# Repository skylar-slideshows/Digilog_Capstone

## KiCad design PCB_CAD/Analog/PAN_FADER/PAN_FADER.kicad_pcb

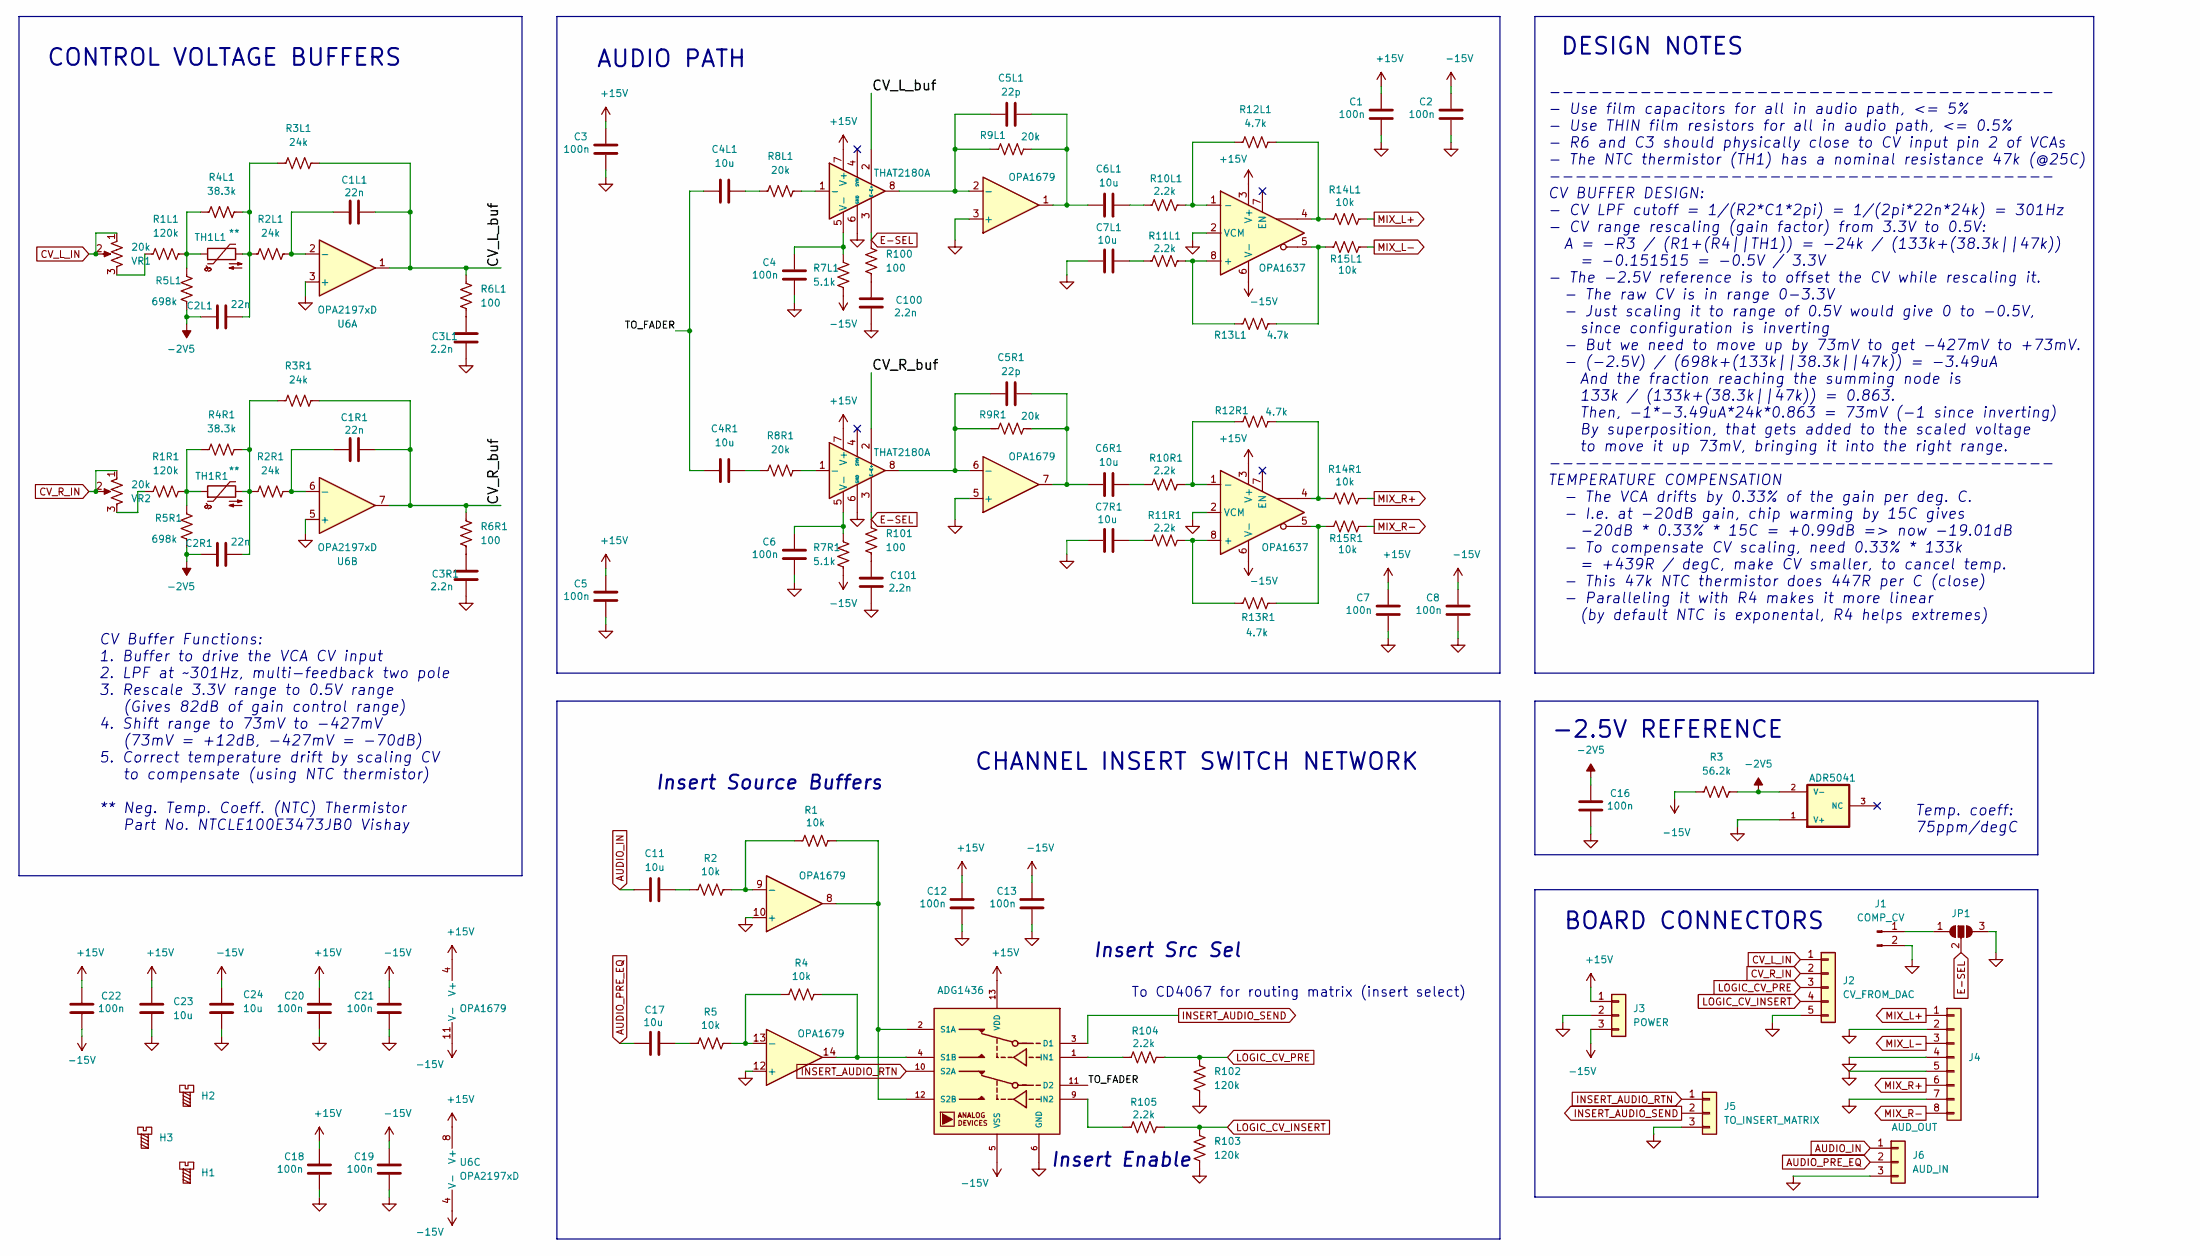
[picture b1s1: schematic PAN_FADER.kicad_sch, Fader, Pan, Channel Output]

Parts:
C1, C2, C3, C4, C5, C6, C7, C8, C12, C13, C16, C18, C19, C20, C21, C22: 100n; C_0603_1608Metric; LCSC C1591
C1L1, C1R1, C2L1, C2R1: 22n; C_Rect_L7.2mm_W2.5mm_P5.00mm; LCSC DNP
C3L1, C3R1, C100, C101: 2.2n; C_0805_2012Metric; LCSC C107103
C4L1, C4R1, C6L1, C6R1, C7L1, C7R1, C11, C17: 10u; CP_Elec_6.3x5.4_Nichicon; LCSC C340735
C5L1, C5R1: 22p; C_0603_1608Metric; LCSC C105620
C23, C24: 10u; C_1206_3216Metric; LCSC C9807
H1, H2, H3: MountingHole_Pad; MountingHole_2.2mm_M2
J1: COMP_CV; PinHeader_1x02_P2.54mm_Vertical; LCSC DNP
J2: CV_FROM_DAC; PinHeader_1x05_P2.54mm_Vertical; Part Number 1-0301FBV0T; LCSC DNP
J3: POWER; PinHeader_1x03_P2.54mm_Vertical; Part Number 1-0301FBV0T; LCSC DNP
J4: AUD_OUT; PinHeader_1x08_P2.54mm_Vertical; Part Number 1-0301FBV0T; LCSC DNP
J5: TO_INSERT_MATRIX; PinHeader_1x03_P2.54mm_Vertical; Part Number 1-0301FBV0T; LCSC DNP
J6: AUD_IN; PinHeader_1x03_P2.54mm_Vertical; Part Number 1-0301FBV0T; LCSC DNP
JP1: SolderJumper_3_Open; SolderJumper-3_P2.0mm_Open_TrianglePad1.0x1.5mm; LCSC DNP
R1, R2, R4, R5, R14L1, R14R1, R15L1, R15R1: 10k; R_0603_1608Metric; LCSC C95204
R1L1, R1R1, R102, R103: 120k; R_0402_1005Metric; LCSC C517522
R2L1, R2R1, R3L1, R3R1: 24k; R_0603_1608Metric; LCSC C319717
R3: 56.2k; R_0402_1005Metric; LCSC C705626
R4L1, R4R1: 38.3k; R_0603_1608Metric; LCSC C861362
R5L1, R5R1: 698k; R_0805_2012Metric; LCSC C865618
R6L1, R6R1, R100, R101: 100; R_0603_1608Metric; LCSC C22775
R7L1, R7R1: 5.1k; R_0603_1608Metric; LCSC C122969
R8L1, R8R1, R9L1, R9R1: 20k; R_0603_1608Metric; LCSC C154077
R10L1, R10R1, R11L1, R11R1, R104, R105: 2.2k; R_0402_1005Metric; LCSC C326602
R12L1, R12R1, R13L1, R13R1: 4.7k; R_0402_1005Metric; LCSC C281778
TH1L1, TH1R1: **; R_Axial_DIN0207_L6.3mm_D2.5mm_P2.54mm_Vertical; LCSC DNP
U1, U5: THAT2180A; SIP-8_19x3mm_P2.54mm; LCSC DNP
U2: OPA1679; SOIC-14_3.9x8.65mm_Pitch1.27mm; LCSC C2878631
U3, U7: OPA1637; Texas_S-PDSO-G8_3x3mm_P0.65mm; LCSC C2860968
U6: OPA2197xD; SOIC-8_3.9x4.9mm_P1.27mm; LCSC C139363
U8: ADR5041; SOT-23-3; MPN ADR5041ARTZ-R2; LCSC C659596
U9: ADG1436; TSSOP-16_4.4x5mm_P0.65mm; LCSC C408899
VR1, VR2: 20k; Potentiometer_Bourns_3314J_Vertical; LCSC C55069

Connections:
+15V: C1.2, C3.2, C5.2, C7.2, C12.2, C18.2, C20.2, C22.2, C23.1, J3.1, U1.7 (V+), U2.4 (V+), U3.3 (V+), U5.7 (V+), U6.8 (V+), U7.3 (V+), U9.13 (VDD)
-2V5: C2L1.1, C2R1.1, C16.2, R3.2, R5L1.1, R5R1.1, U8.2 (V-)
-15V: C2.2, C8.2, C13.2, C19.2, C21.2, C22.1, C24.2, J3.3, R3.1, R7L1.1, R7R1.1, U2.11 (V-), U3.6 (V-), U6.4 (V-), U7.6 (V-), U9.5 (VSS)
/CV_L_buf: C1L1.2, R3L1.2, R6L1.2, U1.2 (E+), U6.1
/CV_R_buf: C1R1.2, R3R1.2, R6R1.2, U5.2 (E+), U6.7
/TO_FADER: C4L1.1, C4R1.1, U9.11 (D2)
AUDIO_IN: C11.1, J6.1
AUDIO_PRE_EQ: C17.1, J6.2
CV_L_IN: J2.1, VR1.1, VR1.2
CV_R_IN: J2.2, VR2.1, VR2.2
E-SEL: JP1.2 (C), R100.2, R101.2, U1.3 (E-), U5.3 (E-)
GND: C1.1, C2.1, C3.1, C3L1.1, C3R1.1, C4.1, C5.1, C6.1, C7.1, C7L1.1, C7R1.1, C8.1, C12.1, C13.1, C16.1, C18.1, C19.1, C20.1, C21.1, C23.2, C24.1, C100.1, C101.1, J1.2, J2.5, J3.2, J4.2, J4.4, J4.5, J4.7, J5.3, J6.3, JP1.3 (B), R102.1, R103.1, U1.6 (GND), U2.3 (+), U2.5 (+), U2.10 (+), U2.12 (+), U3.2 (VCM), U5.6 (GND), U6.3 (+), U6.5 (+), U7.2 (VCM), U8.1 (V+), U9.6 (GND)
INSERT_AUDIO_RTN: J5.1, U9.10 (S2A)
INSERT_AUDIO_SEND: J5.2, U9.3 (D1)
LOGIC_CV_INSERT: J2.4, R103.2, R105.2
LOGIC_CV_PRE: J2.3, R102.2, R104.2
MIX_L+: J4.1, R14L1.2
MIX_L-: J4.3, R15L1.2
MIX_R+: J4.6, R14R1.2
MIX_R-: J4.8, R15R1.2
unnamed: C2L1.2, R2L1.1, R3L1.1, R4L1.2, TH1L1.2
unnamed: C2R1.2, R2R1.1, R3R1.1, R4R1.2, TH1R1.2
unnamed: C3L1.2, R6L1.1
unnamed: C3R1.2, R6R1.1
unnamed: C4L1.2, R8L1.1
unnamed: C4R1.2, R8R1.1
unnamed: C5L1.2, C6L1.1, R9L1.2, U2.1
unnamed: C5R1.2, C6R1.1, R9R1.2, U2.7
unnamed: C6L1.2, R10L1.1
unnamed: C6R1.2, R10R1.1
unnamed: C7L1.2, R11L1.1
unnamed: C7R1.2, R11R1.1
unnamed: C11.2, R2.2
unnamed: C17.2, R5.2
unnamed: C100.2, R100.1
unnamed: C101.2, R101.1
unnamed: J1.1, JP1.1 (A)
unnamed: R1L1.1, VR1.3
unnamed: R1L1.2, R4L1.1, R5L1.2, TH1L1.1
unnamed: R1R1.1, VR2.3
unnamed: R1R1.2, R4R1.1, R5R1.2, TH1R1.1
unnamed: R12L1.2, R14L1.1, U3.4
unnamed: R12R1.2, R14R1.1, U7.4
unnamed: R13L1.2, R15L1.1, U3.5
unnamed: R13R1.2, R15R1.1, U7.5
unnamed: R8L1.2, U1.1 (-)
unnamed: C4.2, R7L1.2, U1.5 (V-)
unnamed: C5L1.1, R9L1.1, U1.8, U2.2 (-)
unnamed: C5R1.1, R9R1.1, U2.6 (-), U5.8
unnamed: R1.2, R2.1, U2.9 (-)
unnamed: R4.2, R5.1, U2.13 (-)
unnamed: R11L1.2, R13L1.1, U3.8 (+)
unnamed: R10L1.2, R12L1.1, U3.1 (-)
unnamed: R8R1.2, U5.1 (-)
unnamed: C6.2, R7R1.2, U5.5 (V-)
unnamed: C1L1.1, R2L1.2, U6.2 (-)
unnamed: C1R1.1, R2R1.2, U6.6 (-)
unnamed: R11R1.2, R13R1.1, U7.8 (+)
unnamed: R10R1.2, R12R1.1, U7.1 (-)
unnamed: R104.1, U9.1 (IN1)
unnamed: R105.1, U9.9 (IN2)
unnamed: R1.1, U2.8, U9.2 (S1A), U9.12 (S2B)
unnamed: R4.1, U2.14, U9.4 (S1B)

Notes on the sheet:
CONTROL VOLTAGE BUFFERS
--------------------------------------- - Use film capacitors for all in audio path, <= 5% - Use THIN film resistors for all in audio path, <= 0.5% - R6 and C3 should physically close to CV input pin 2 of VCAs - The NTC thermistor (TH1) has a nominal resistance 47k (@25C) --------------------------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
BOARD CONNECTORS
CV Buffer Functions: 1. Buffer to drive the VCA CV input 2. LPF at ~301Hz, multi-feedback two pole 3. Rescale 3.3V range to 0.5V range (Gives 82dB of gain control range) 4. Shift range to 73mV to -427mV (73mV = +12dB, -427mV = -70dB) 5. Correct temperature drift by scaling CV to compensate (using N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
Insert Source Buffers
Insert Enable
AUDIO PATH
Insert Src Sel
-2.5V REFERENCE
CHANNEL INSERT SWITCH NETWORK
Temp. coeff: 75ppm/degC
DESIGN NOTES
To CD4067 for routing matrix (insert select)

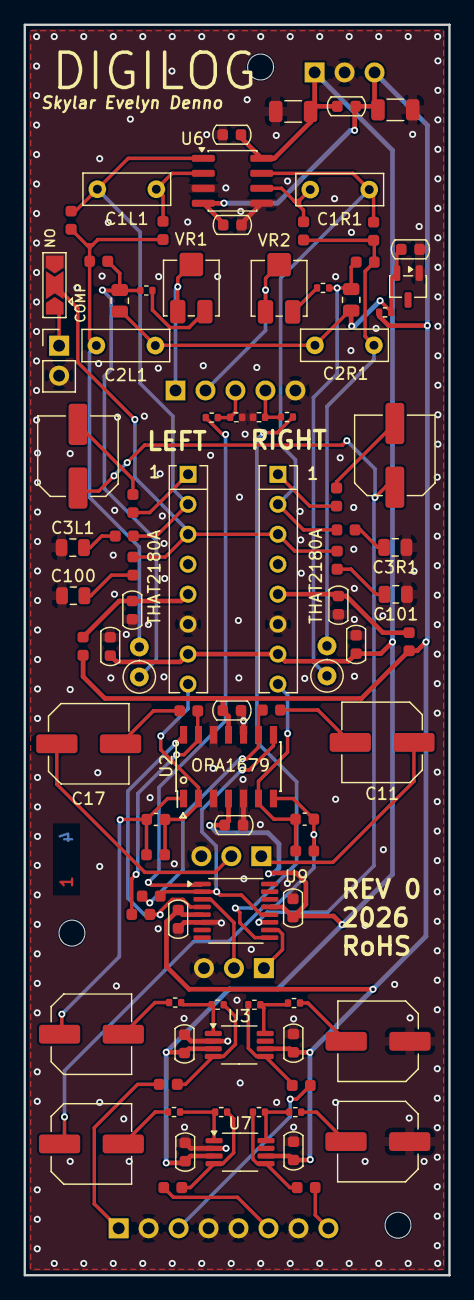
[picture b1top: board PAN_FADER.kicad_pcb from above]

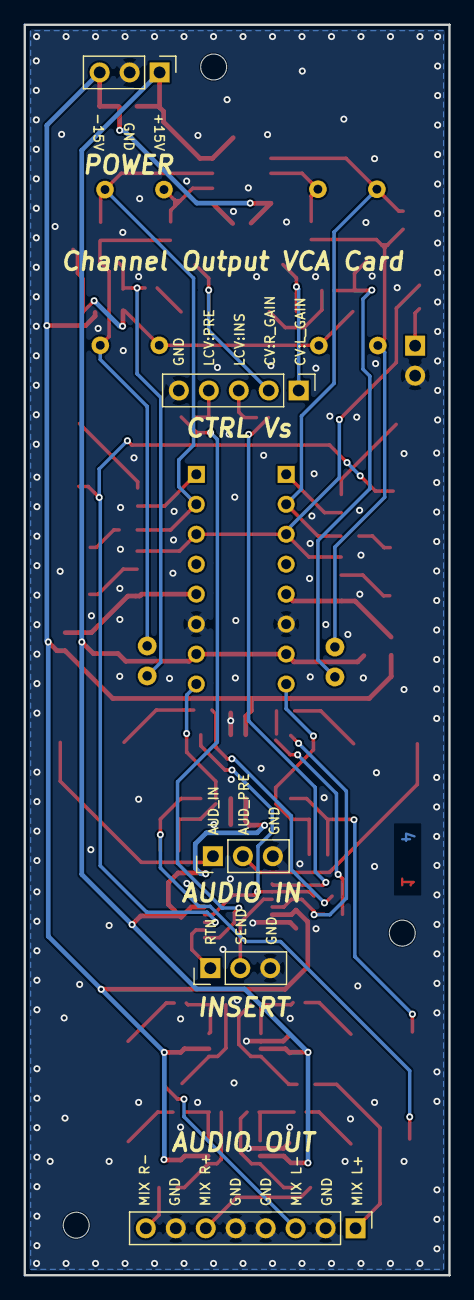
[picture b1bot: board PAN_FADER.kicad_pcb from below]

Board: 4 copper layers, 36.0 x 106.0 mm, 99 parts (5 on the bottom side), 63 nets.

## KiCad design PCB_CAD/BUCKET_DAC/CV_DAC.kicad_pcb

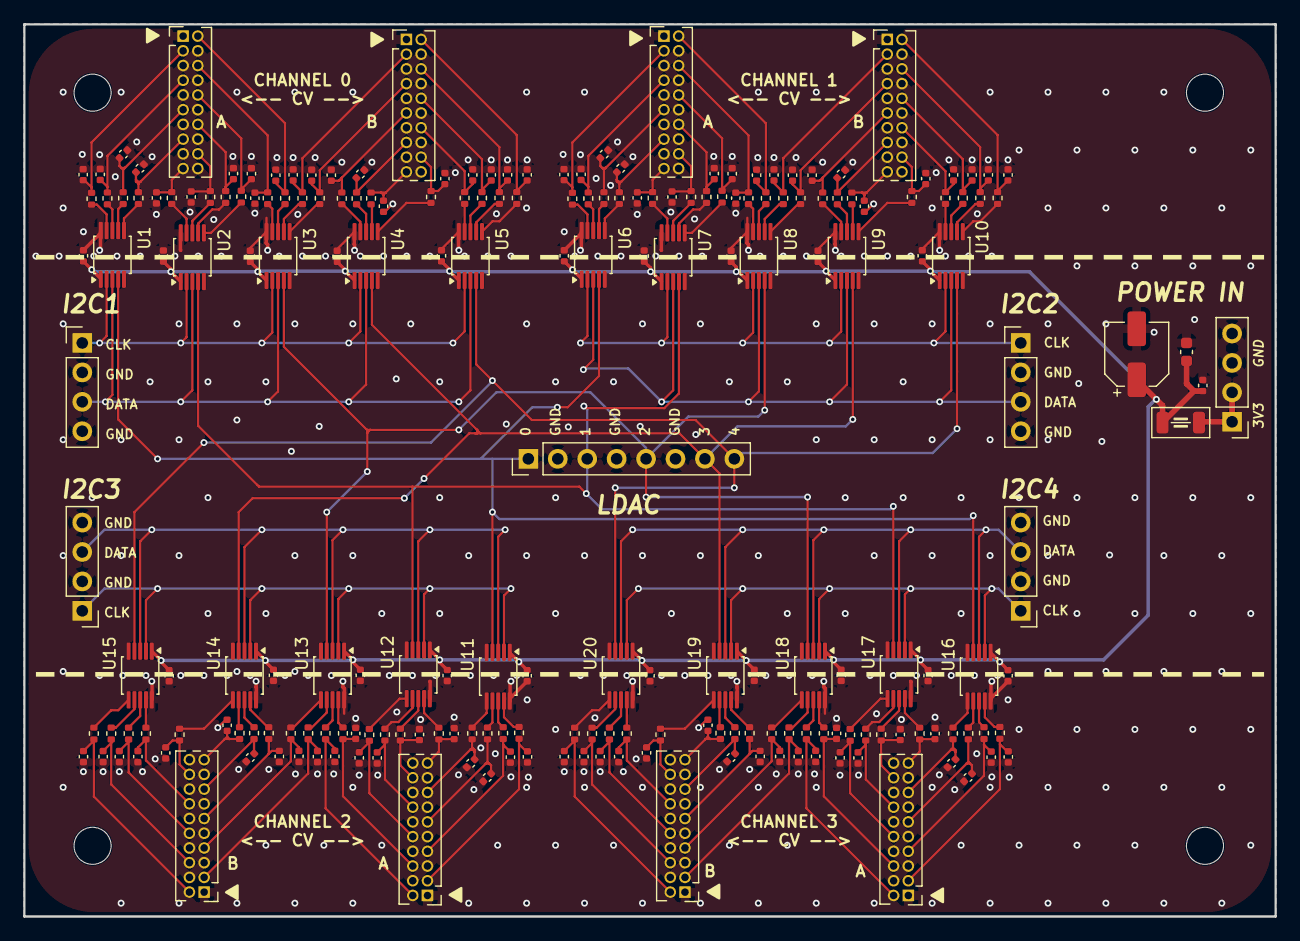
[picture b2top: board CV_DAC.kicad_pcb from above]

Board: 4 copper layers, 108.0 x 77.0 mm, 222 parts (0 on the bottom side), 176 nets.

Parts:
C1, C6, C11, C16, C21, C26, C27, C28, C29, C46, C51, C52, C53, C54, C71, C76, C77, C78, C79, C96, C103: 100n; C_0402_1005Metric
C2, C3, C4, C5, C7, C8, C9, C10, C12, C13, C14, C15, C17, C18, C19, C20, C22, C23, C24, C25, C30, C31, C32, C33, C34, C35, C36, C37, C38, C39, C40, C41, C42, C43, C44, C45, C47, C48, C49, C50, C55, C56, C57, C58, C59, C60, C61, C62, C63, C64, C65, C66, C67, C68, C69, C70, C72, C73, C74, C75, C80, C81, C82, C83, C84, C85, C86, C87, C88, C89, C90, C91, C92, C93, C94, C95, C97, C98, C99, C100: 10n; C_0402_1005Metric
C101: 22u; CP_Elec_5x5.4
C102: 1u; C_0603_1608Metric
FB1: Ferrite_Bead; Ferrite_1206_3216Metric
H1, H2, H3, H4: MountingScrew; MountingHole_3.2mm_M3
J1: Channel_0_CV_Out1; PinHeader_2x10_P1.27mm_Vertical
J2: Channel_0_CV_Out2; PinHeader_2x10_P1.27mm_Vertical
J3: Channel_1_CV_Out1; PinHeader_2x10_P1.27mm_Vertical
J4: Channel_1_CV_Out2; PinHeader_2x10_P1.27mm_Vertical
J5: Channel_2_CV_Out1; PinHeader_2x10_P1.27mm_Vertical
J6: Channel_2_CV_Out2; PinHeader_2x10_P1.27mm_Vertical
J7: Channel_3_CV_Out1; PinHeader_2x10_P1.27mm_Vertical
J8: Channel_3_CV_Out2; PinHeader_2x10_P1.27mm_Vertical
J9: I2C1; PinHeader_1x04_P2.54mm_Vertical
J10: I2C2; PinHeader_1x04_P2.54mm_Vertical
J11: I2C3; PinHeader_1x04_P2.54mm_Vertical
J12: I2C4; PinHeader_1x04_P2.54mm_Vertical
J13: POWER_IN; PinHeader_1x04_P2.54mm_Vertical
J14: LDAC; PinHeader_1x08_P2.54mm_Vertical
R1, R2, R3, R4, R5, R6, R7, R8, R9, R10, R11, R12, R13, R14, R15, R16, R17, R18, R19, R20, R21, R22, R23, R24, R25, R26, R27, R28, R29, R30, R31, R32, R33, R34, R35, R36, R37, R38, R39, R40, R41, R42, R43, R44, R45, R46, R47, R48, R49, R50, R51, R52, R53, R54, R55, R56, R57, R58, R59, R60, R61, R62, R63, R64, R65, R66, R67, R68, R69, R70, R71, R72, R73, R74, R75, R76, R77, R78, R79, R80: 470; R_0402_1005Metric
U1, U2, U3, U4, U5, U6, U7, U8, U9, U10, U11, U12, U13, U14, U15, U16, U17, U18, U19, U20: MCP4728; MSOP-10_3x3mm_P0.5mm

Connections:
+3V3: C1.1, C6.1, C11.1, C16.1, C21.1, C26.1, C27.1, C28.1, C29.1, C46.1, C51.1, C52.1, C53.1, C54.1, C71.1, C76.1, C77.1, C78.1, C79.1, C96.1, C101.1, C102.1, C103.1, FB1.2, U1.1 (VDD), U2.1 (VDD), U3.1 (VDD), U4.1 (VDD), U5.1 (VDD), U6.1 (VDD), U7.1 (VDD), U8.1 (VDD), U9.1 (VDD), U10.1 (VDD), U11.1 (VDD), U12.1 (VDD), U13.1 (VDD), U14.1 (VDD), U15.1 (VDD), U16.1 (VDD), U17.1 (VDD), U18.1 (VDD), U19.1 (VDD), U20.1 (VDD)
+3V3IN: FB1.1, J13.1, J13.2
CV0_CH0: C2.1, J1.15, R1.2
CV0_CH1: C30.1, J3.15, R21.2
CV0_CH2: C55.1, J5.15, R41.2
CV0_CH3: C80.1, J7.15, R61.2
CV1_CH0: C3.1, J1.11, R2.2
CV1_CH1: C31.1, J3.11, R22.2
CV1_CH2: C56.1, J5.11, R42.2
CV1_CH3: C81.1, J7.11, R62.2
CV2_CH0: C4.1, J1.7, R3.2
CV2_CH1: C32.1, J3.7, R23.2
CV2_CH2: C57.1, J5.7, R43.2
CV2_CH3: C82.1, J7.7, R63.2
CV3_CH0: C5.1, J1.3, R4.2
CV3_CH1: C33.1, J3.3, R24.2
CV3_CH2: C58.1, J5.3, R44.2
CV3_CH3: C83.1, J7.3, R64.2
CV4_CH0: C7.1, J1.10, R5.2
CV4_CH1: C34.1, J3.10, R25.2
CV4_CH2: C59.1, J5.10, R45.2
CV4_CH3: C84.1, J7.10, R65.2
CV5_CH0: C8.1, J1.14, R6.2
CV5_CH1: C35.1, J3.14, R26.2
CV5_CH2: C60.1, J5.14, R46.2
CV5_CH3: C85.1, J7.14, R66.2
CV6_CH0: C9.1, J1.18, R7.2
CV6_CH1: C36.1, J3.18, R27.2
CV6_CH2: C61.1, J5.18, R47.2
CV6_CH3: C86.1, J7.18, R67.2
CV7_CH0: C10.1, J1.19, R8.2
CV7_CH1: C37.1, J3.19, R28.2
CV7_CH2: C62.1, J5.19, R48.2
CV7_CH3: C87.1, J7.19, R68.2
CV8_CH0: C12.1, J2.7, R9.2
CV8_CH1: C38.1, J4.7, R29.2
CV8_CH2: C63.1, J6.7, R49.2
CV8_CH3: C88.1, J8.7, R69.2
CV9_CH0: C13.1, J2.3, R10.2
CV9_CH1: C39.1, J4.3, R30.2
CV9_CH2: C64.1, J6.3, R50.2
CV9_CH3: C89.1, J8.3, R70.2
CV10_CH0: C14.1, J1.2, R11.2
CV10_CH1: C40.1, J3.2, R31.2
CV10_CH2: C65.1, J5.2, R51.2
CV10_CH3: C90.1, J7.2, R71.2
CV11_CH0: C15.1, J1.6, R12.2
CV11_CH1: C41.1, J3.6, R32.2
CV11_CH2: C66.1, J5.6, R52.2
CV11_CH3: C91.1, J7.6, R72.2
CV12_CH0: C17.1, J2.18, R13.2
CV12_CH1: C42.1, J4.18, R33.2
CV12_CH2: C67.1, J6.18, R53.2
CV12_CH3: C92.1, J8.18, R73.2
CV13_CH0: C18.1, J2.19, R14.2
CV13_CH1: C43.1, J4.19, R34.2
CV13_CH2: C68.1, J6.19, R54.2
CV13_CH3: C93.1, J8.19, R74.2
CV14_CH0: C19.1, J2.15, R15.2
CV14_CH1: C44.1, J4.15, R35.2
CV14_CH2: C69.1, J6.15, R55.2
CV14_CH3: C94.1, J8.15, R75.2
CV15_CH0: C20.1, J2.11, R16.2
CV15_CH1: C45.1, J4.11, R36.2
CV15_CH2: C70.1, J6.11, R56.2
CV15_CH3: C95.1, J8.11, R76.2
CV16_CH0: C22.1, J2.2, R17.2
CV16_CH1: C47.1, J4.2, R37.2
CV16_CH2: C72.1, J6.2, R57.2
CV16_CH3: C97.1, J8.2, R77.2
CV17_CH0: C23.1, J2.6, R18.2
CV17_CH1: C48.1, J4.6, R38.2
CV17_CH2: C73.1, J6.6, R58.2
CV17_CH3: C98.1, J8.6, R78.2
CV18_CH0: C24.1, J2.10, R19.2
CV18_CH1: C49.1, J4.10, R39.2
CV18_CH2: C74.1, J6.10, R59.2
CV18_CH3: C99.1, J8.10, R79.2
CV19_CH0: C25.1, J2.14, R20.2
CV19_CH1: C50.1, J4.14, R40.2
CV19_CH2: C75.1, J6.14, R60.2
CV19_CH3: C100.1, J8.14, R80.2
GND: C1.2, C2.2, C3.2, C4.2, C5.2, C6.2, C7.2, C8.2, C9.2, C10.2, C11.2, C12.2, C13.2, C14.2, C15.2, C16.2, C17.2, C18.2, C19.2, C20.2, C21.2, C22.2, C23.2, C24.2, C25.2, C26.2, C27.2, C28.2, C29.2, C30.2, C31.2, C32.2, C33.2, C34.2, C35.2, C36.2, C37.2, C38.2, C39.2, C40.2, C41.2, C42.2, C43.2, C44.2, C45.2, C46.2, C47.2, C48.2, C49.2, C50.2, C51.2, C52.2, C53.2, C54.2, C55.2, C56.2, C57.2, C58.2, C59.2, C60.2, C61.2, C62.2, C63.2, C64.2, C65.2, C66.2, C67.2, C68.2, C69.2, C70.2, C71.2, C72.2, C73.2, C74.2, C75.2, C76.2, C77.2, C78.2, C79.2, C80.2, C81.2, C82.2, C83.2, C84.2, C85.2, C86.2, C87.2, C88.2, C89.2, C90.2, C91.2, C92.2, C93.2, C94.2, C95.2, C96.2, C97.2, C98.2, C99.2, C100.2, C101.2, C102.2, C103.2, J1.1, J1.4, J1.5, J1.8, J1.9, J1.12, J1.13, J1.16, J1.17, J1.20, J2.1, J2.4, J2.5, J2.8, J2.9, J2.12, J2.13, J2.16, J2.17, J2.20, J3.1, J3.4, J3.5, J3.8, J3.9, J3.12, J3.13, J3.16, J3.17, J3.20, J4.1, J4.4, J4.5, J4.8, J4.9, J4.12, J4.13, J4.16, J4.17, J4.20, J5.1, J5.4, J5.5, J5.8, J5.9, J5.12, J5.13, J5.16, J5.17, J5.20, J6.1, J6.4, J6.5, J6.8, J6.9, J6.12, J6.13, J6.16, J6.17, J6.20, J7.1, J7.4, J7.5, J7.8, J7.9, J7.12, J7.13, J7.16, J7.17, J7.20, J8.1, J8.4, J8.5, J8.8, J8.9, J8.12, J8.13, J8.16, J8.17, J8.20, J9.2, J9.4, J10.2, J10.4, J11.2, J11.4, J12.2, J12.4, J13.3, J13.4, J14.2, J14.4, J14.6, U1.10 (VSS), U2.10 (VSS), U3.10 (VSS), U4.10 (VSS), U5.10 (VSS), U6.10 (VSS), U7.10 (VSS), U8.10 (VSS), U9.10 (VSS), U10.10 (VSS), U11.10 (VSS), U12.10 (VSS), U13.10 (VSS), U14.10 (VSS), U15.10 (VSS), U16.10 (VSS), U17.10 (VSS), U18.10 (VSS), U19.10 (VSS), U20.10 (VSS)
I2C1_CLK: J9.1, U1.2 (SCL), U2.2 (SCL), U3.2 (SCL), U4.2 (SCL), U5.2 (SCL)
I2C1_DAT: J9.3, U1.3 (SDA), U2.3 (SDA), U3.3 (SDA), U4.3 (SDA), U5.3 (SDA)
I2C2_CLK: J10.1, U6.2 (SCL), U7.2 (SCL), U8.2 (SCL), U9.2 (SCL), U10.2 (SCL)
I2C2_DAT: J10.3, U6.3 (SDA), U7.3 (SDA), U8.3 (SDA), U9.3 (SDA), U10.3 (SDA)
I2C3_CLK: J11.1, U11.2 (SCL), U12.2 (SCL), U13.2 (SCL), U14.2 (SCL), U15.2 (SCL)
I2C3_DAT: J11.3, U11.3 (SDA), U12.3 (SDA), U13.3 (SDA), U14.3 (SDA), U15.3 (SDA)
I2C4_CLK: J12.1, U16.2 (SCL), U17.2 (SCL), U18.2 (SCL), U19.2 (SCL), U20.2 (SCL)
I2C4_DAT: J12.3, U16.3 (SDA), U17.3 (SDA), U18.3 (SDA), U19.3 (SDA), U20.3 (SDA)
LDAC0_CHAN0: J14.1, U1.4 (~LDAC), U6.4 (~LDAC), U11.4 (~LDAC), U16.4 (~LDAC)
LDAC1_CHAN0: J14.3, U2.4 (~LDAC), U7.4 (~LDAC), U12.4 (~LDAC), U17.4 (~LDAC)
LDAC2_CHAN0: J14.5, U3.4 (~LDAC), U8.4 (~LDAC), U13.4 (~LDAC), U18.4 (~LDAC)
LDAC3_CHAN0: J14.7, U4.4 (~LDAC), U9.4 (~LDAC), U14.4 (~LDAC), U19.4 (~LDAC)
LDAC4_CHAN0: J14.8, U5.4 (~LDAC), U10.4 (~LDAC), U15.4 (~LDAC), U20.4 (~LDAC)
unnamed: R1.1, U1.6 (VOUTA)
unnamed: R2.1, U1.7 (VOUTB)
unnamed: R3.1, U1.8 (VOUTC)
unnamed: R4.1, U1.9 (VOUTD)
unnamed: R5.1, U2.6 (VOUTA)
unnamed: R6.1, U2.7 (VOUTB)
unnamed: R7.1, U2.8 (VOUTC)
unnamed: R8.1, U2.9 (VOUTD)
unnamed: R9.1, U3.6 (VOUTA)
unnamed: R10.1, U3.7 (VOUTB)
unnamed: R11.1, U3.8 (VOUTC)
unnamed: R12.1, U3.9 (VOUTD)
unnamed: R13.1, U4.6 (VOUTA)
unnamed: R14.1, U4.7 (VOUTB)
unnamed: R15.1, U4.8 (VOUTC)
unnamed: R16.1, U4.9 (VOUTD)
unnamed: R17.1, U5.6 (VOUTA)
unnamed: R18.1, U5.7 (VOUTB)
unnamed: R19.1, U5.8 (VOUTC)
unnamed: R20.1, U5.9 (VOUTD)
unnamed: R21.1, U6.6 (VOUTA)
unnamed: R22.1, U6.7 (VOUTB)
unnamed: R23.1, U6.8 (VOUTC)
unnamed: R24.1, U6.9 (VOUTD)
unnamed: R25.1, U7.6 (VOUTA)
unnamed: R26.1, U7.7 (VOUTB)
unnamed: R27.1, U7.8 (VOUTC)
unnamed: R28.1, U7.9 (VOUTD)
unnamed: R29.1, U8.6 (VOUTA)
unnamed: R30.1, U8.7 (VOUTB)
unnamed: R31.1, U8.8 (VOUTC)
unnamed: R32.1, U8.9 (VOUTD)
unnamed: R33.1, U9.6 (VOUTA)
unnamed: R34.1, U9.7 (VOUTB)
unnamed: R35.1, U9.8 (VOUTC)
unnamed: R36.1, U9.9 (VOUTD)
unnamed: R37.1, U10.6 (VOUTA)
unnamed: R38.1, U10.7 (VOUTB)
unnamed: R39.1, U10.8 (VOUTC)
unnamed: R40.1, U10.9 (VOUTD)
unnamed: R41.1, U11.6 (VOUTA)
unnamed: R42.1, U11.7 (VOUTB)
unnamed: R43.1, U11.8 (VOUTC)
unnamed: R44.1, U11.9 (VOUTD)
unnamed: R45.1, U12.6 (VOUTA)
unnamed: R46.1, U12.7 (VOUTB)
unnamed: R47.1, U12.8 (VOUTC)
unnamed: R48.1, U12.9 (VOUTD)
unnamed: R49.1, U13.6 (VOUTA)
unnamed: R50.1, U13.7 (VOUTB)
unnamed: R51.1, U13.8 (VOUTC)
unnamed: R52.1, U13.9 (VOUTD)
unnamed: R53.1, U14.6 (VOUTA)
unnamed: R54.1, U14.7 (VOUTB)
unnamed: R55.1, U14.8 (VOUTC)
unnamed: R56.1, U14.9 (VOUTD)
unnamed: R57.1, U15.6 (VOUTA)
unnamed: R58.1, U15.7 (VOUTB)
unnamed: R59.1, U15.8 (VOUTC)
unnamed: R60.1, U15.9 (VOUTD)
unnamed: R61.1, U16.6 (VOUTA)
unnamed: R62.1, U16.7 (VOUTB)
unnamed: R63.1, U16.8 (VOUTC)
unnamed: R64.1, U16.9 (VOUTD)
unnamed: R65.1, U17.6 (VOUTA)
unnamed: R66.1, U17.7 (VOUTB)
unnamed: R67.1, U17.8 (VOUTC)
unnamed: R68.1, U17.9 (VOUTD)
unnamed: R69.1, U18.6 (VOUTA)
unnamed: R70.1, U18.7 (VOUTB)
unnamed: R71.1, U18.8 (VOUTC)
unnamed: R72.1, U18.9 (VOUTD)
unnamed: R73.1, U19.6 (VOUTA)
unnamed: R74.1, U19.7 (VOUTB)
unnamed: R75.1, U19.8 (VOUTC)
unnamed: R76.1, U19.9 (VOUTD)
unnamed: R77.1, U20.6 (VOUTA)
unnamed: R78.1, U20.7 (VOUTB)
unnamed: R79.1, U20.8 (VOUTC)
unnamed: R80.1, U20.9 (VOUTD)

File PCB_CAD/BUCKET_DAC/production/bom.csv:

Designator,Footprint,Quantity,Value,LCSC Part #
"C1, C103, C11, C16, C21, C26, C27, C28, C29, C46, C51, C52, C53, C54, C6, C71, C76, C77, C78, C79, C96",0402,21,100n,C1525
"C10, C100, C12, C13, C14, C15, C17, C18, C19, C2, C20, C22, C23, C24, C25, C3, C30, C31, C32, C33, C34, C35, C36, C37, C38, C39, C4, C40, C41, C42, C43, C44, C45, C47, C48, C49, C5, C50, C55, C56, C57, C58, C59, C60, C61, C62, C63, C64, C65, C66, C67, C68, C69, C7, C70, C72, C73, C74, C75, C8, C80, C81, C82, C83, C84, C85, C86, C87, C88, C89, C9, C90, C91, C92, C93, C94, C95, C97, C98, C99",0402,80,10n,C1524
C101,CP_Elec_5x5.4,1,22u,C23289
C102,0603,1,1u,C1592
FB1,Ferrite_1206_3216Metric,1,Ferrite_Bead,C16902
J1,PinHeader_2x10_P1.27mm_Vertical,1,Channel_0_CV_Out1,
J10,PinHeader_1x04_P2.54mm_Vertical,1,I2C2,
J11,PinHeader_1x04_P2.54mm_Vertical,1,I2C3,
J12,PinHeader_1x04_P2.54mm_Vertical,1,I2C4,
J13,PinHeader_1x04_P2.54mm_Vertical,1,POWER_IN,
J14,PinHeader_1x08_P2.54mm_Vertical,1,LDAC,
J2,PinHeader_2x10_P1.27mm_Vertical,1,Channel_0_CV_Out2,
J3,PinHeader_2x10_P1.27mm_Vertical,1,Channel_1_CV_Out1,
J4,PinHeader_2x10_P1.27mm_Vertical,1,Channel_1_CV_Out2,
J5,PinHeader_2x10_P1.27mm_Vertical,1,Channel_2_CV_Out1,
J6,PinHeader_2x10_P1.27mm_Vertical,1,Channel_2_CV_Out2,
J7,PinHeader_2x10_P1.27mm_Vertical,1,Channel_3_CV_Out1,
J8,PinHeader_2x10_P1.27mm_Vertical,1,Channel_3_CV_Out2,
J9,PinHeader_1x04_P2.54mm_Vertical,1,I2C1,
"R1, R10, R11, R12, R13, R14, R15, R16, R17, R18, R19, R2, R20, R21, R22, R23, R24, R25, R26, R27, R28, R29, R3, R30, R31, R32, R33, R34, R35, R36, R37, R38, R39, R4, R40, R41, R42, R43, R44, R45, R46, R47, R48, R49, R5, R50, R51, R52, R53, R54, R55, R56, R57, R58, R59, R6, R60, R61, R62, R63, R64, R65, R66, R67, R68, R69, R7, R70, R71, R72, R73, R74, R75, R76, R77, R78, R79, R8, R80, R9",0402,80,470,C25117
"U1, U10, U11, U12, U13, U14, U15, U16, U17, U18, U19, U2, U20, U3, U4, U5, U6, U7, U8, U9",MSOP-10_3x3mm_P0.5mm,20,MCP4728,C108207

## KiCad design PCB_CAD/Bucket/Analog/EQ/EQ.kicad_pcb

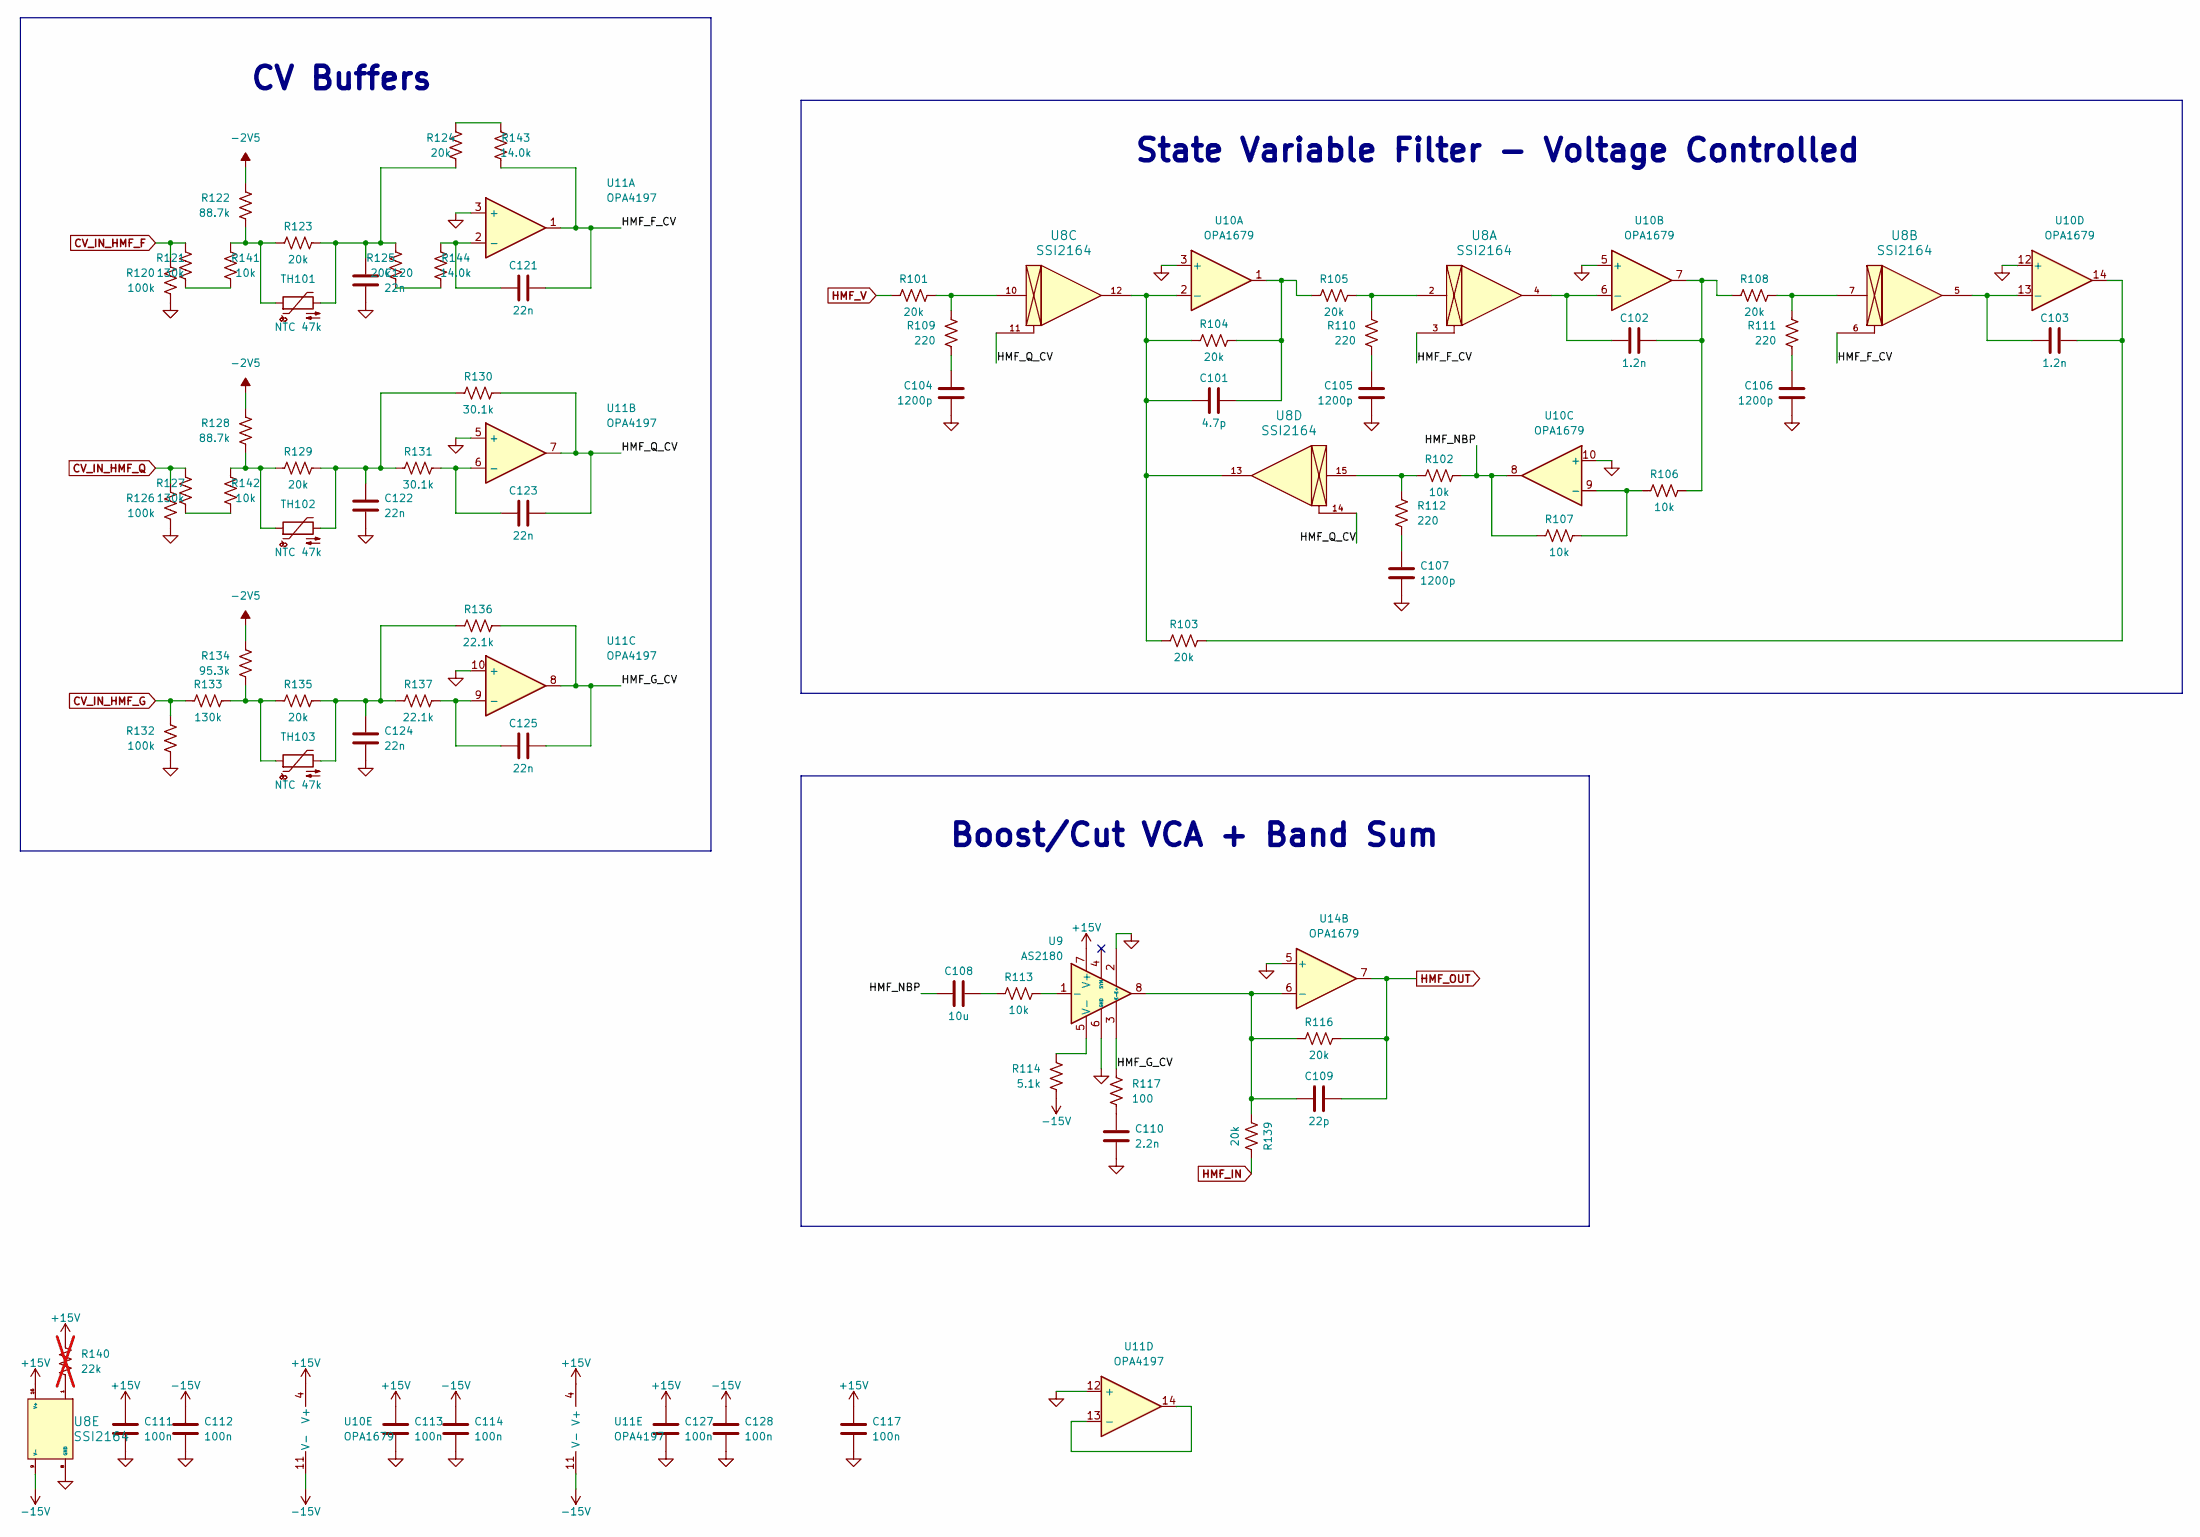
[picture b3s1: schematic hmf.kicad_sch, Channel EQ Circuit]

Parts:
C101: 4.7p; C_0603_1608Metric; LCSC C282071
C102, C103: 1.2n; C_1206_3216Metric; LCSC C527278
C104, C105, C106, C107: 1200p; C_1206_3216Metric; LCSC C527278
C108: 10u; CP_Elec_6.3x5.4_Nichicon; LCSC C340735
C109: 22p; C_0603_1608Metric; LCSC C105620
C110: 2.2n; C_0805_2012Metric; LCSC C107103
C111, C112, C113, C114, C117, C127, C128: 100n; C_0603_1608Metric; LCSC C1591
C120, C121, C122, C123, C124, C125: 22n; C_Rect_L7.2mm_W2.5mm_P5.00mm; LCSC dnp
R101, R103, R104, R105, R108, R116, R123, R124, R125, R129, R135, R139: 20k; R_0603_1608Metric
R102, R106, R107, R113, R141, R142: 10k; R_0603_1608Metric
R109, R110, R111, R112: 220; R_0603_1608Metric
R114: 5.1k; R_0603_1608Metric
R117: 100; R_0603_1608Metric
R120, R126, R132: 100k; R_0603_1608Metric
R121, R127, R133: 130k; R_0603_1608Metric
R122, R128: 88.7k; R_0603_1608Metric
R130, R131: 30.1k; R_0603_1608Metric
R134: 95.3k; R_0603_1608Metric
R136, R137: 22.1k; R_0603_1608Metric
R140: 22k; R_0603_1608Metric; not fitted
R143, R144: 14.0k; R_0603_1608Metric
TH101, TH102, TH103: NTC 47k; R_Axial_DIN0207_L6.3mm_D2.5mm_P2.54mm_Vertical; MPN NTCLE100E3473JB0; LCSC dnp
U8: SSI2164; SOIC-16_3.9x9.9mm_Pitch1.27mm; LCSC dnp
U9: AS2180; SOIC-8-1EP_3.9x4.9mm_P1.27mm_EP2.29x3mm_ThermalVias; LCSC dnp
U10, U14: OPA1679; SOIC-14_3.9x8.7mm_P1.27mm; LCSC C2057264
U11: OPA4197; SOIC-14_3.9x8.7mm_P1.27mm; LCSC C2058532

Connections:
+15V: C111.1, C113.1, C117.1, C127.1, R140.1, U8.16 (V+), U9.7 (V+), U10.4 (V+), U11.4 (V+); also elsewhere on the board
-2V5: R122.1, R128.1, R134.1; also elsewhere on the board
-15V: C112.1, C114.1, C128.1, R114.2, U8.9 (V-), U10.11 (V-), U11.11 (V-); also elsewhere on the board
/HMF/HMF_F_CV: C121.2, R143.2, U8.3, U8.6, U11.1
/HMF/HMF_G_CV: C125.2, R117.1, R136.2, U9.3 (E-), U11.8
/HMF/HMF_NBP: C108.1, R102.2, R107.1, U10.8
/HMF/HMF_Q_CV: C123.2, R130.2, U8.11, U8.14, U11.7
CV_IN_HMF_F: R120.1, R121.1
CV_IN_HMF_G: R132.1, R133.1
CV_IN_HMF_Q: R126.1, R127.1
GND: C104.2, C105.2, C106.2, C107.2, C110.2, C111.2, C112.2, C113.2, C114.2, C117.2, C120.2, C122.2, C124.2, C127.2, C128.2, R120.2, R126.2, R132.2, U8.8 (GND), U9.2 (E+), U9.6 (GND), U10.3 (+), U10.5 (+), U10.10 (+), U10.12 (+), U11.3 (+), U11.5 (+), U11.10 (+), U11.12 (+), U14.5 (+); also elsewhere on the board
HMF_IN: R139.2
HMF_OUT: C109.2, R116.2, U14.7
HMF_V: R101.1
unnamed: C101.2, R104.2, R105.1, U10.1
unnamed: C102.2, R106.2, R108.1, U10.7
unnamed: C103.2, R103.2, U10.14
unnamed: C104.1, R109.2
unnamed: C105.1, R110.2
unnamed: C106.1, R111.2
unnamed: C107.1, R112.2
unnamed: C108.2, R113.1
unnamed: C110.1, R117.2
unnamed: C120.1, R123.2, R124.1, R125.1, TH101.2
unnamed: C122.1, R129.2, R130.1, R131.1, TH102.2
unnamed: C124.1, R135.2, R136.1, R137.1, TH103.2
unnamed: R101.2, R109.1, U8.10
unnamed: R102.1, R112.1, U8.15
unnamed: R105.2, R110.1, U8.2
unnamed: R108.2, R111.1, U8.7
unnamed: R121.2, R141.1
unnamed: R122.2, R123.1, R141.2, TH101.1
unnamed: R124.2, R143.1
unnamed: R125.2, R144.1
unnamed: R127.2, R142.1
unnamed: R128.2, R129.1, R142.2, TH102.1
unnamed: R133.2, R134.2, R135.1, TH103.1
unnamed: R140.2, U8.1
unnamed: R113.2, U9.1 (-)
unnamed: R114.1, U9.5 (V-)
unnamed: C101.1, R103.1, R104.1, U8.12, U8.13, U10.2 (-)
unnamed: C102.1, U8.4, U10.6 (-)
unnamed: R106.1, R107.2, U10.9 (-)
unnamed: C103.1, U8.5, U10.13 (-)
unnamed: C121.1, R144.2, U11.2 (-)
unnamed: C123.1, R131.2, U11.6 (-)
unnamed: C125.1, R137.2, U11.9 (-)
unnamed: U11.13 (-), U11.14
unnamed: C109.1, R116.1, R139.1, U9.8, U14.6 (-)

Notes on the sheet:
State Variable Filter - Voltage Controlled
CV Buffers
Boost/Cut VCA + Band Sum
